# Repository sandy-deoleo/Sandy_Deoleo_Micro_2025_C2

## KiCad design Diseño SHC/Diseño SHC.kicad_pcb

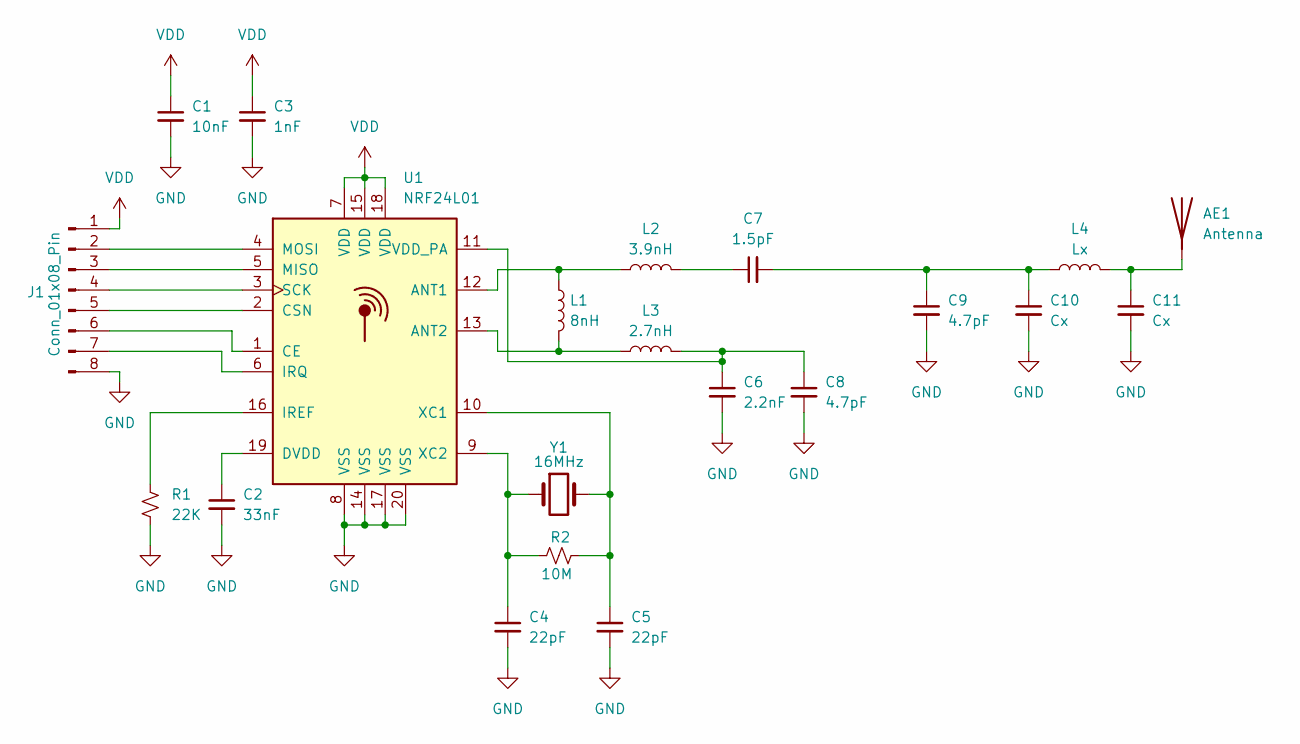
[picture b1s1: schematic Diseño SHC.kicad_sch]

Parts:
AE1: Antenna; Texas_SWRA117D_2.4GHz_Right
C1: 10nF; C_0402_1005Metric
C2: 33nF; C_0402_1005Metric
C3: 1nF; C_0402_1005Metric
C4, C5: 22pF; C_0402_1005Metric
C6: 2.2nF; C_0402_1005Metric
C7: 1.5pF; C_0402_1005Metric
C8, C9: 4.7pF; C_0402_1005Metric
C10, C11: Cx; C_0402_1005Metric
J1: Conn_01x08_Pin; Hirose_DF13-08P-1.25DSA_1x08_P1.25mm_Vertical
L1: 8nH; L_0402_1005Metric
L2: 3.9nH; L_0402_1005Metric
L3: 2.7nH; L_0402_1005Metric
L4: Lx; L_0402_1005Metric
R1: 22K; R_0402_1005Metric
R2: 10M; R_0402_1005Metric
U1: NRF24L01; QFN-20-1EP_4x4mm_P0.5mm_EP2.5x2.5mm
Y1: 16MHz; Crystal_SMD_3215-2Pin_3.2x1.5mm

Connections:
GND: C1.2, C2.2, C3.2, C4.2, C5.2, C6.2, C8.2, C9.2, C10.2, C11.2, J1.8, R1.2, U1.8 (VSS), U1.14 (VSS), U1.17 (VSS), U1.20 (VSS)
unnamed: AE1.1 (A), C11.1, L4.2
unnamed: C7.1, L2.2
unnamed: C7.2, C9.1, C10.1, L4.1
unnamed: J1.2, U1.4 (MOSI)
unnamed: J1.3, U1.5 (MISO)
unnamed: J1.4, U1.3 (SCK)
unnamed: J1.5, U1.2 (CSN)
unnamed: J1.6, U1.1 (CE)
unnamed: J1.7, U1.6 (IRQ)
unnamed: L1.1, L2.1, U1.12 (ANT1)
unnamed: L1.2, L3.1, U1.13 (ANT2)
unnamed: C2.1, U1.19 (DVDD)
unnamed: R1.1, U1.16 (IREF)
unnamed: C6.1, C8.1, L3.2, U1.11 (VDD_PA)
unnamed: C5.1, R2.2, U1.10 (XC1), Y1.2
unnamed: C4.1, R2.1, U1.9 (XC2), Y1.1
VDD: C1.1, C3.1, J1.1, U1.7 (VDD), U1.15 (VDD), U1.18 (VDD)

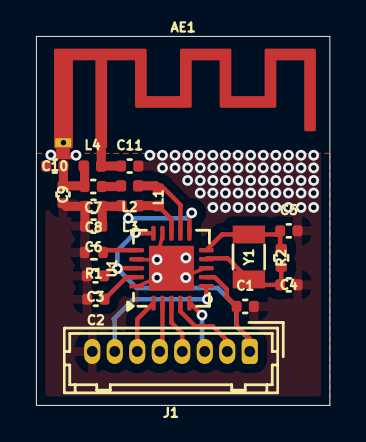
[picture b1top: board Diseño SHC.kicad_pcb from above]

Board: 2 copper layers, 16.3 x 20.5 mm, 21 parts (0 on the bottom side), 18 nets.

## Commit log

2025-06-27 Primer commit
2025-06-27 Segundo commit, correccion de Diseño SHC
2025-06-27 Tercer commit Temporizador video
2025-06-27 Tercer commit Timmer_video
2025-06-28 Cuarto commit, Eliminando lenguajes indeseados
2025-06-28 Cuarto commit, arreglo de todo
2025-07-03 Actualizacion de micro_puerta
2025-07-10 Quinto commit, Tarea 5 y arreglos de PCB
2025-07-17 Sexto commit, Actualización de archivos y ADS
2025-07-17 Septimo commit, MQTT5, WS, MS, TIMMER
2025-08-07 septimo commit, Investigaciones, muestreo y calculo y ejercicios PWM
2025-08-07 octavo commit, ejercicios sobre punteros y enumeracion
2025-08-21 Videos FreeRTOOS
